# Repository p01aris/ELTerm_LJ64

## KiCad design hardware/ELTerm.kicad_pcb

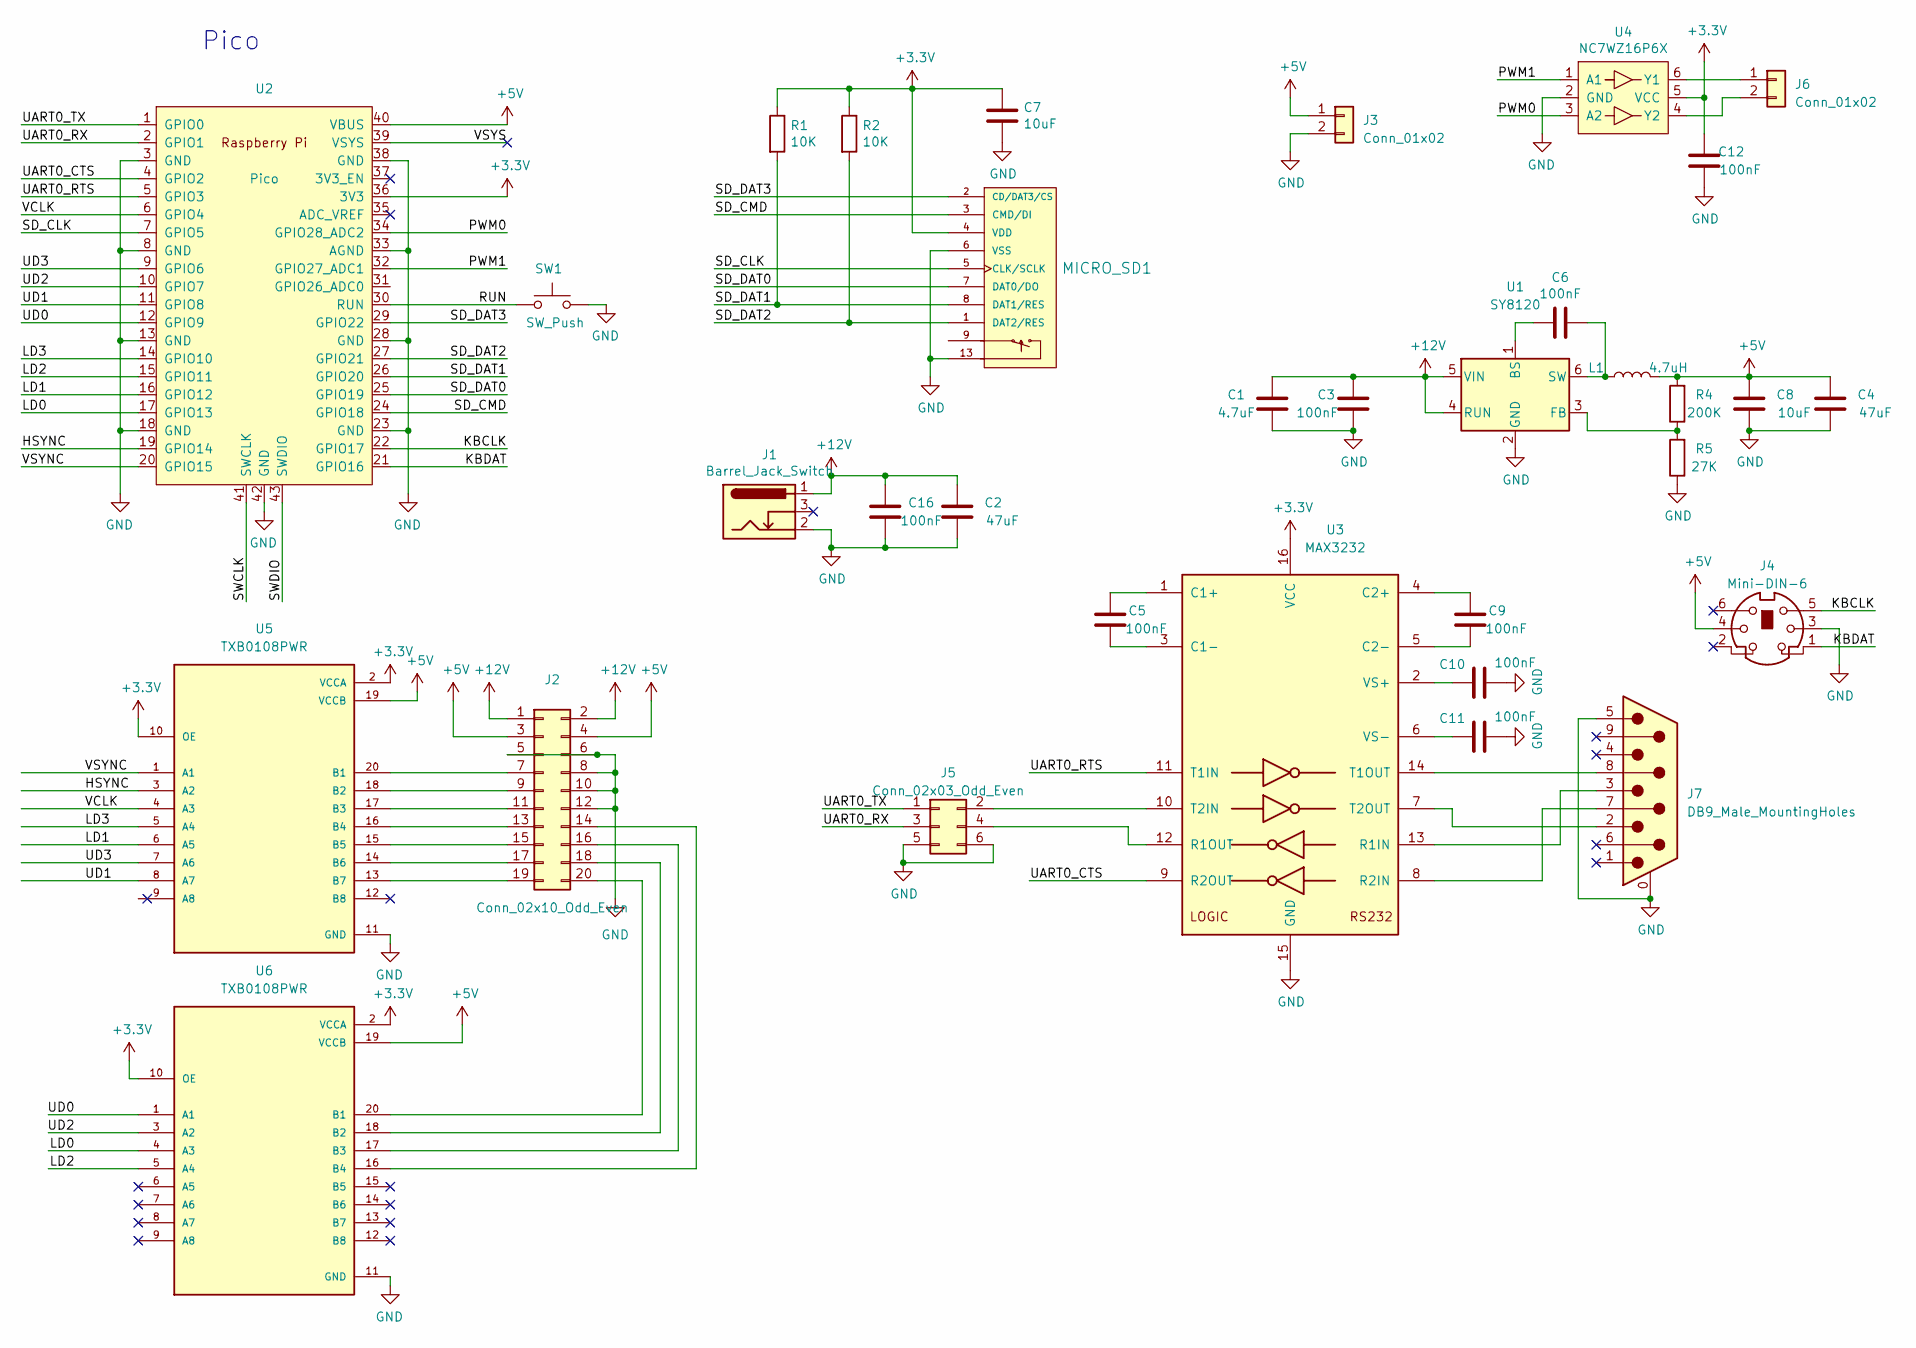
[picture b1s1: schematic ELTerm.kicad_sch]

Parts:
C1: 4.7uF; C_0805_2012Metric
C2, C4: 47uF; C_Elec_5x5.8
C3, C5, C6, C9, C10, C11, C12, C16: 100nF; C_0603_1608Metric
C7, C8: 10uF; C_0603_1608Metric
J1: Barrel_Jack_Switch; BarrelJack_Horizontal
J2: Conn_02x10_Odd_Even; PinHeader_2x10_P2.00mm_Vertical
J3, J6: Conn_01x02; PinHeader_1x02_P2.54mm_Vertical
J4: Mini-DIN-6; MINI-DIN-6-FULL-SHIELD
J5: Conn_02x03_Odd_Even; PinHeader_2x03_P2.54mm_Vertical
J7: DB9_Male_MountingHoles; DSUB-9_Male_Horizontal_P2.77x2.84mm_EdgePinOffset4.94mm_Hou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
L1: 4.7uH; L_Vishay_IHLP-1212
MICRO_SD1: MICRO_SD(TFC-WPAPR-08); TFC-WPAPR-08
R1, R2: 10K; R_0603_1608Metric
R4: 200K; R_0603_1608Metric
R5: 27K; R_0603_1608Metric
SW1: SW_Push; SW_SPST_CK_RS282G05A3
U1: SY8120; TSOT-23-6
U2: Pico; RPi_Pico_SMD_TH
U3: MAX3232; SO-16_3.9x9.9mm_P1.27mm
U4: NC7WZ16P6X; SOT-363_SC-70-6
U5, U6: TXB0108PWR; SOP65P640X120-20N

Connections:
+3V3: C7.1, C12.2, MICRO_SD1.4 (VDD), R1.1, R2.1, U2.36 (3V3), U3.16 (VCC), U4.5 (VCC), U5.2 (VCCA), U5.10 (OE), U6.2 (VCCA), U6.10 (OE)
+5V: C4.2, C8.2, J2.3, J2.4, J3.1, J4.4, L1.2, R4.2, U2.40 (VBUS), U5.19 (VCCB), U6.19 (VCCB)
+12V: C1.2, C2.2, C3.2, C16.2, J1.1, J2.1, J2.2, U1.4 (RUN), U1.5 (VIN)
/HSYNC: U2.19 (GPIO14), U5.3 (A2)
/KBCLK: J4.5, U2.22 (GPIO17)
/KBDAT: J4.1, U2.21 (GPIO16)
/LD0: U2.17 (GPIO13), U6.4 (A3)
/LD1: U2.16 (GPIO12), U5.6 (A5)
/LD2: U2.15 (GPIO11), U6.5 (A4)
/LD3: U2.14 (GPIO10), U5.5 (A4)
/PWM0: U2.34 (GPIO28_ADC2), U4.3 (A2)
/PWM1: U2.32 (GPIO27_ADC1), U4.1 (A1)
/RUN: SW1.1, U2.30 (RUN)
/SD_CLK: MICRO_SD1.5 (CLK/SCLK), U2.7 (GPIO5)
/SD_CMD: MICRO_SD1.3 (CMD/DI), U2.24 (GPIO18)
/SD_DAT0: MICRO_SD1.7 (DAT0/DO), U2.25 (GPIO19)
/SD_DAT1: MICRO_SD1.8 (DAT1/RES), R1.2, U2.26 (GPIO20)
/SD_DAT2: MICRO_SD1.1 (DAT2/RES), R2.2, U2.27 (GPIO21)
/SD_DAT3: MICRO_SD1.2 (CD/DAT3/CS), U2.29 (GPIO22)
/SWCLK: U2.41 (SWCLK)
/SWDIO: U2.43 (SWDIO)
/UART0_CTS: U2.4 (GPIO2), U3.9 (R2OUT)
/UART0_RTS: U2.5 (GPIO3), U3.11 (T1IN)
/UART0_RX: J5.3, U2.2 (GPIO1)
/UART0_TX: J5.1, U2.1 (GPIO0)
/UD0: U2.12 (GPIO9), U6.1 (A1)
/UD1: U2.11 (GPIO8), U5.8 (A7)
/UD2: U2.10 (GPIO7), U6.3 (A2)
/UD3: U2.9 (GPIO6), U5.7 (A6)
/VCLK: U2.6 (GPIO4), U5.4 (A3)
/VSYNC: U2.20 (GPIO15), U5.1 (A1)
/VSYS: U2.39 (VSYS)
GND: C1.1, C2.1, C3.1, C4.1, C7.2, C8.1, C10.1, C11.1, C12.1, C16.1, J1.2, J2.5, J2.6, J2.8, J2.10, J2.12, J3.2, J4.3, J5.5, J5.6, J7.0 (PAD), J7.5, MICRO_SD1.6 (VSS), MICRO_SD1.10, MICRO_SD1.11, MICRO_SD1.12, MICRO_SD1.13, R5.1, SW1.2, U1.2 (GND), U2.3 (GND), U2.8 (GND), U2.13 (GND), U2.18 (GND), U2.23 (GND), U2.28 (GND), U2.33 (AGND), U2.38 (GND), U2.42 (GND), U3.15 (GND), U4.2 (GND), U5.11 (GND), U6.11 (GND)
unnamed: J2.7, U5.20 (B1)
unnamed: J2.9, U5.18 (B2)
unnamed: J2.11, U5.17 (B3)
unnamed: J2.13, U5.16 (B4)
unnamed: J2.14, U6.16 (B4)
unnamed: J2.15, U5.15 (B5)
unnamed: J2.16, U6.17 (B3)
unnamed: J2.17, U5.14 (B6)
unnamed: J2.18, U6.18 (B2)
unnamed: J2.19, U5.13 (B7)
unnamed: J2.20, U6.20 (B1)
unnamed: J5.2, U3.10 (T2IN)
unnamed: J5.4, U3.12 (R1OUT)
unnamed: J6.1, U4.6 (Y1)
unnamed: J6.2, U4.4 (Y2)
unnamed: C6.2, U1.1 (BS)
unnamed: R4.1, R5.2, U1.3 (FB)
unnamed: C6.1, L1.1, U1.6 (SW)
unnamed: C5.2, U3.1 (C1+)
unnamed: C5.1, U3.3 (C1-)
unnamed: C9.2, U3.4 (C2+)
unnamed: C9.1, U3.5 (C2-)
unnamed: J7.3, U3.13 (R1IN)
unnamed: J7.7, U3.8 (R2IN)
unnamed: J7.8, U3.14 (T1OUT)
unnamed: J7.2, U3.7 (T2OUT)
unnamed: C10.2, U3.2 (VS+)
unnamed: C11.2, U3.6 (VS-)

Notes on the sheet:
Pico

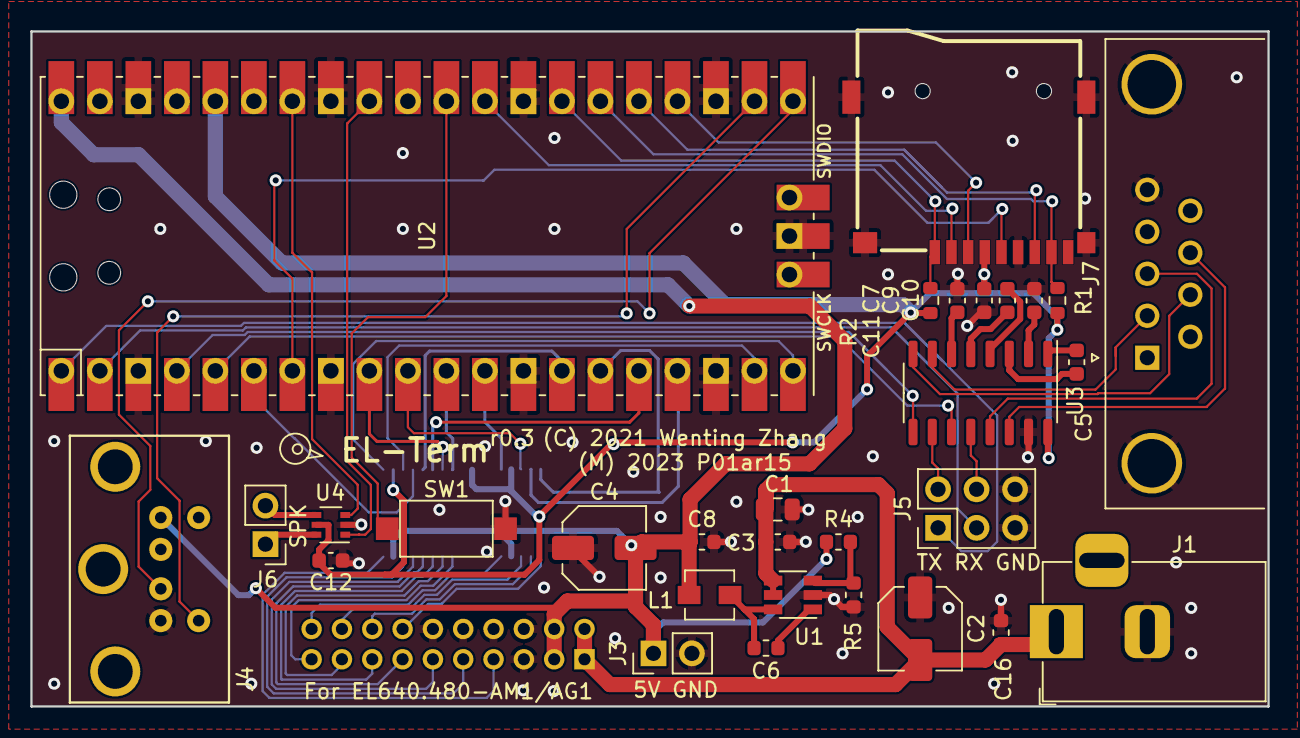
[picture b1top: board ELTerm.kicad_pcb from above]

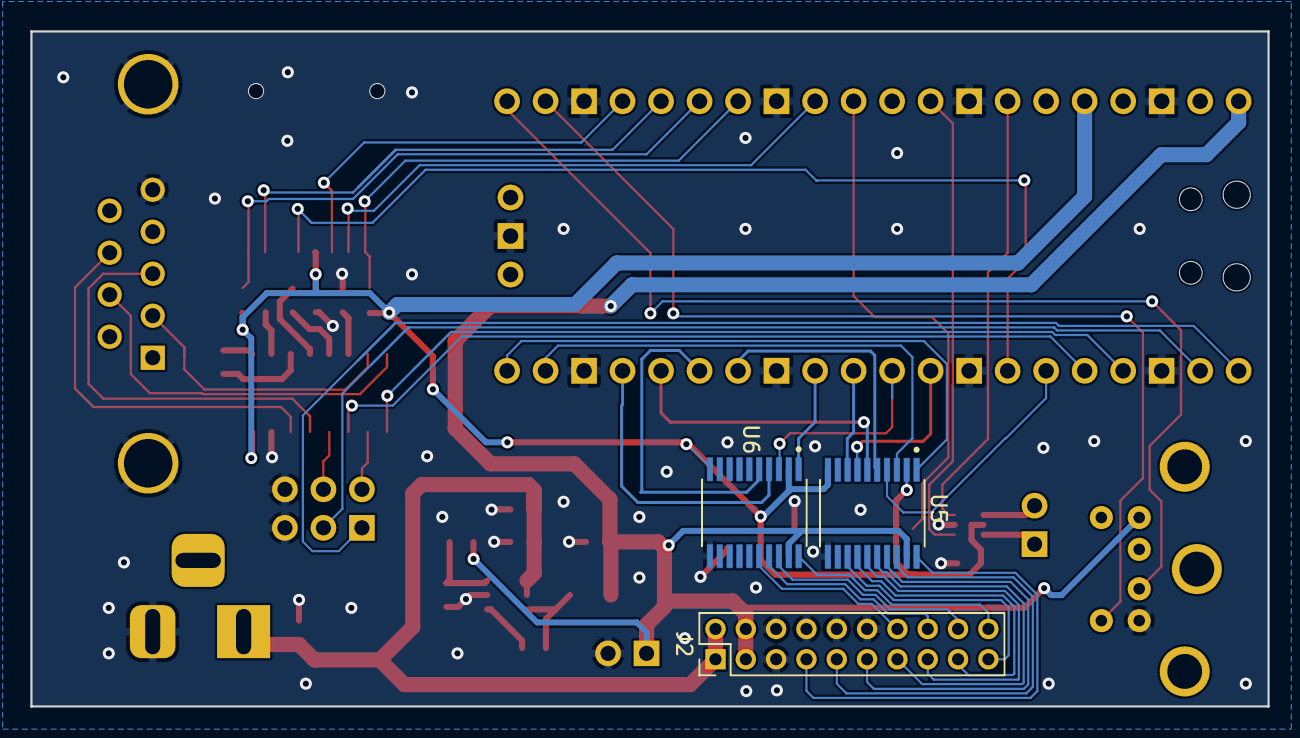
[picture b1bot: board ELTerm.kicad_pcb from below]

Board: 2 copper layers, 81.6 x 44.5 mm, 33 parts (3 on the bottom side), 58 nets.

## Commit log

2023-10-17 Adapt EL screen to sharp LJ64
2025-03-06 Created using Colab

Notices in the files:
hardware/ELTerm.kicad_pcb:
(C) 2021 Wenting Zhang
